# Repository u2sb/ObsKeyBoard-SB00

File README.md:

OBS 专业导播键盘，包括硬件 + 软件，适合个人 DIY，价格便宜 500 以内即可搞定。

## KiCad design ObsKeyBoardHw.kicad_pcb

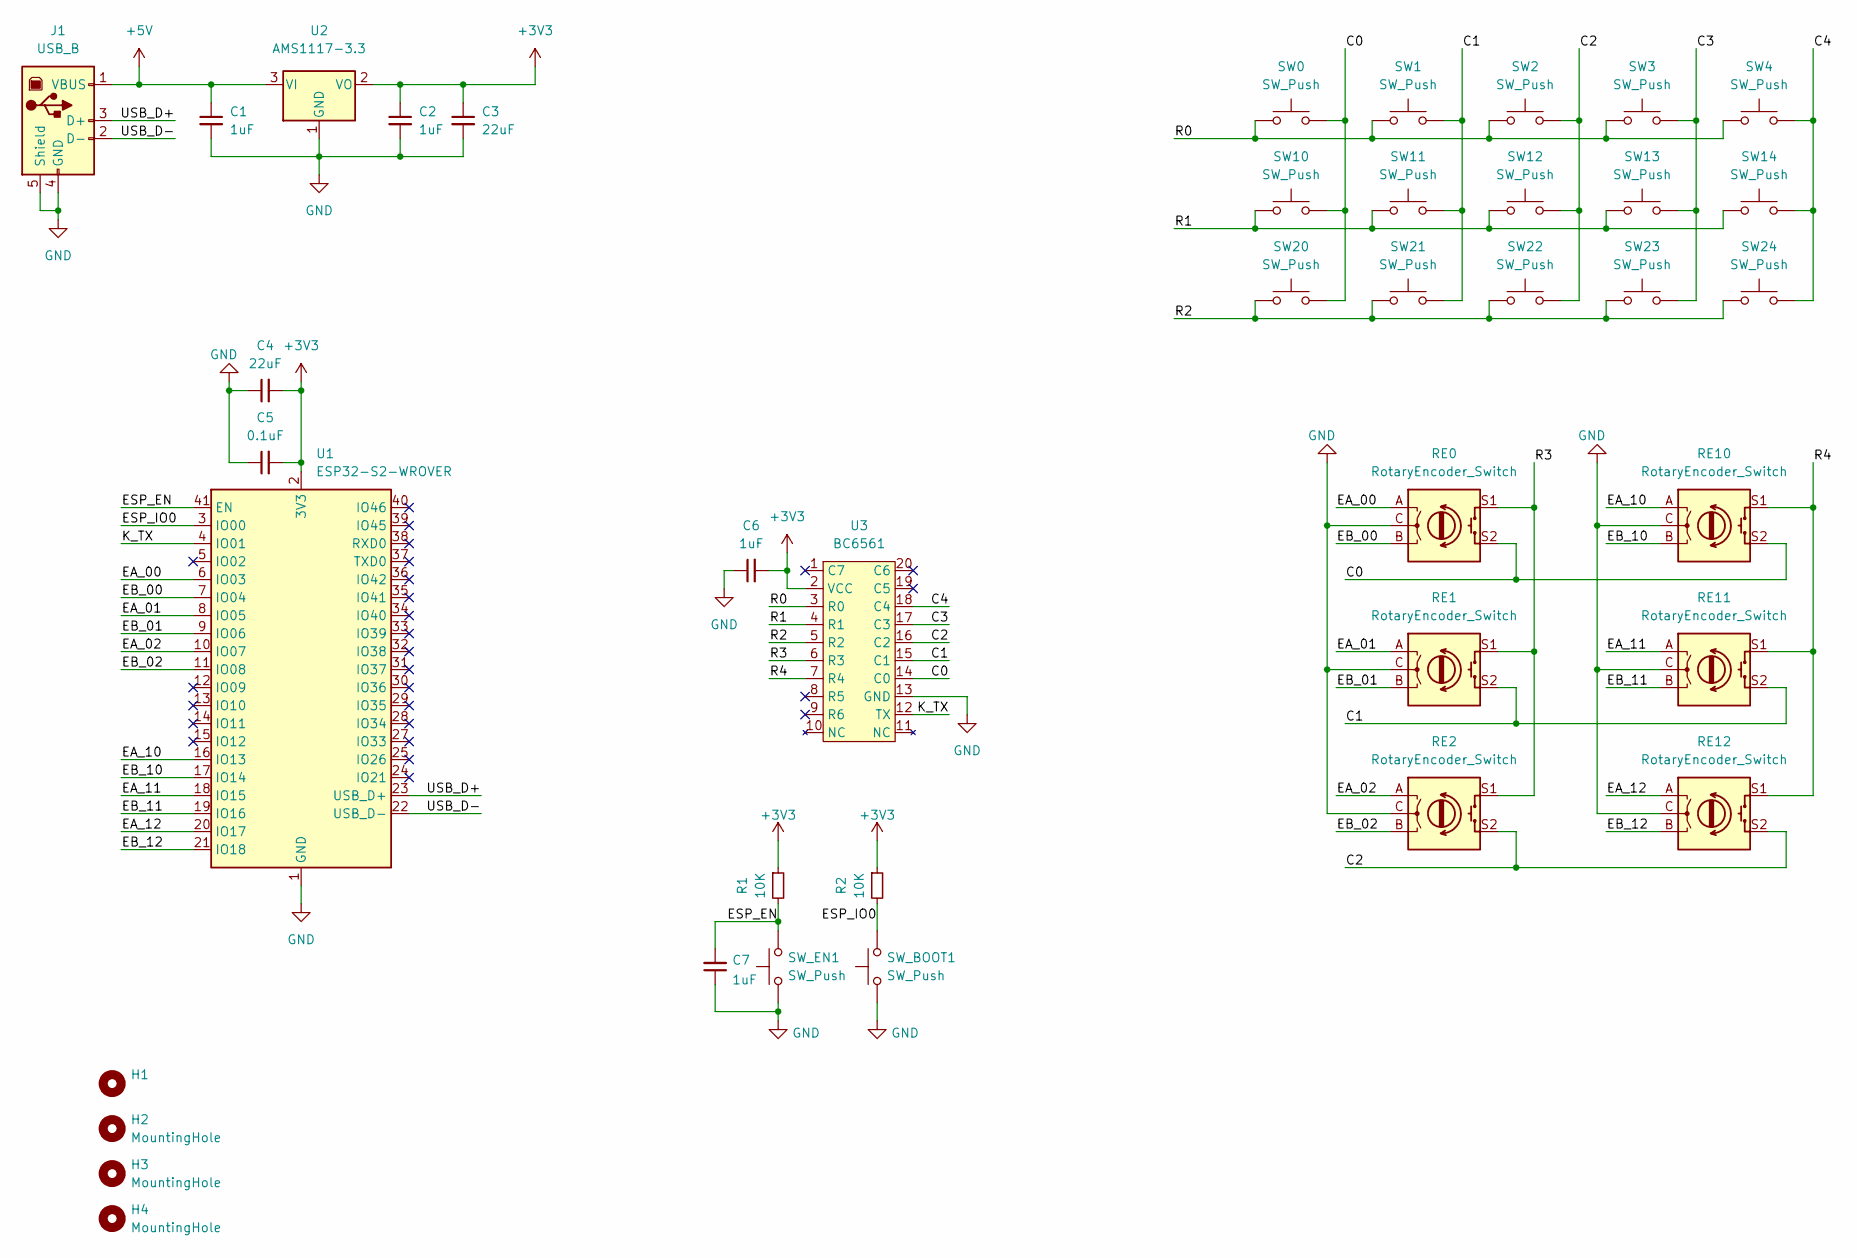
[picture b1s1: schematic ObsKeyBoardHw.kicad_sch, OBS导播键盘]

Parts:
C1, C2, C6, C7: 1uF; C_0805_2012Metric
C3, C4: 22uF; C_0805_2012Metric
C5: 0.1uF; C_0805_2012Metric
H1: (no value)
H2, H3, H4: MountingHole; MountingHole_3.2mm_M3_ISO7380
J1: USB_B; USB_B_Lumberg_2411_02_Horizontal
R1, R2: 10K; R_0805_2012Metric
RE0, RE1, RE2, RE10, RE11, RE12: RotaryEncoder_Switch; RotaryEncoder_Alps_EC11E-Switch_Vertical_H20mm
SW0, SW1, SW2, SW3, SW4, SW10, SW11, SW12, SW13, SW14, SW20, SW21, SW22, SW23, SW24: SW_Push; SW_Cherry_MX_1.00u_Plate
SW_BOOT1: SW_Push; SW_SPST_CK_RS282G05A3
SW_EN1: SW_Push; SW_SPST_CK_RS282G05A3
U1: ESP32-S2-WROVER
U2: AMS1117-3.3; SOT-223-3_TabPin2
U3: BC6561; SSOP-20_5.3x7.2mm_P0.65mm

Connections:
+3V3: C2.1, C3.1, C4.2, C5.2, C6.2, R1.1, R2.1, U1.2 (3V3), U2.2 (VO), U3.2 (VCC)
+5V: C1.1, J1.1 (VBUS), U2.3 (VI)
/C0: RE0.S2, RE10.S2, SW0.2, SW10.2, SW20.2, U3.14 (C0)
/C1: RE1.S2, RE11.S2, SW1.2, SW11.2, SW21.2, U3.15 (C1)
/C2: RE2.S2, RE12.S2, SW2.2, SW12.2, SW22.2, U3.16 (C2)
/C3: SW3.2, SW13.2, SW23.2, U3.17 (C3)
/C4: SW4.2, SW14.2, SW24.2, U3.18 (C4)
/EA_00: RE0.A, U1.6 (IO03)
/EA_01: RE1.A, U1.8 (IO05)
/EA_02: RE2.A, U1.10 (IO07)
/EA_10: RE10.A, U1.16 (IO13)
/EA_11: RE11.A, U1.18 (IO15)
/EA_12: RE12.A, U1.20 (IO17)
/EB_00: RE0.B, U1.7 (IO04)
/EB_01: RE1.B, U1.9 (IO06)
/EB_02: RE2.B, U1.11 (IO08)
/EB_10: RE10.B, U1.17 (IO14)
/EB_11: RE11.B, U1.19 (IO16)
/EB_12: RE12.B, U1.21 (IO18)
/ESP_EN: C7.2, R1.2, SW_EN1.2, U1.41 (EN)
/ESP_IO0: R2.2, SW_BOOT1.2, U1.3 (IO00)
/K_TX: U1.4 (IO01), U3.12 (TX)
/R0: SW0.1, SW1.1, SW2.1, SW3.1, SW4.1, U3.3 (R0)
/R1: SW10.1, SW11.1, SW12.1, SW13.1, SW14.1, U3.4 (R1)
/R2: SW20.1, SW21.1, SW22.1, SW23.1, SW24.1, U3.5 (R2)
/R3: RE0.S1, RE1.S1, RE2.S1, U3.6 (R3)
/R4: RE10.S1, RE11.S1, RE12.S1, U3.7 (R4)
/USB_D+: J1.3 (D+), U1.23 (USB_D+)
/USB_D-: J1.2 (D-), U1.22 (USB_D-)
GND: C1.2, C2.2, C3.2, C4.1, C5.1, C6.1, C7.1, J1.4 (GND), J1.5 (Shield), RE0.C, RE1.C, RE2.C, RE10.C, RE11.C, RE12.C, SW_BOOT1.1, SW_EN1.1, U1.1 (GND), U1.26 (GND), U1.42 (GND), U1.43 (GND), U2.1 (GND), U3.13 (GND)

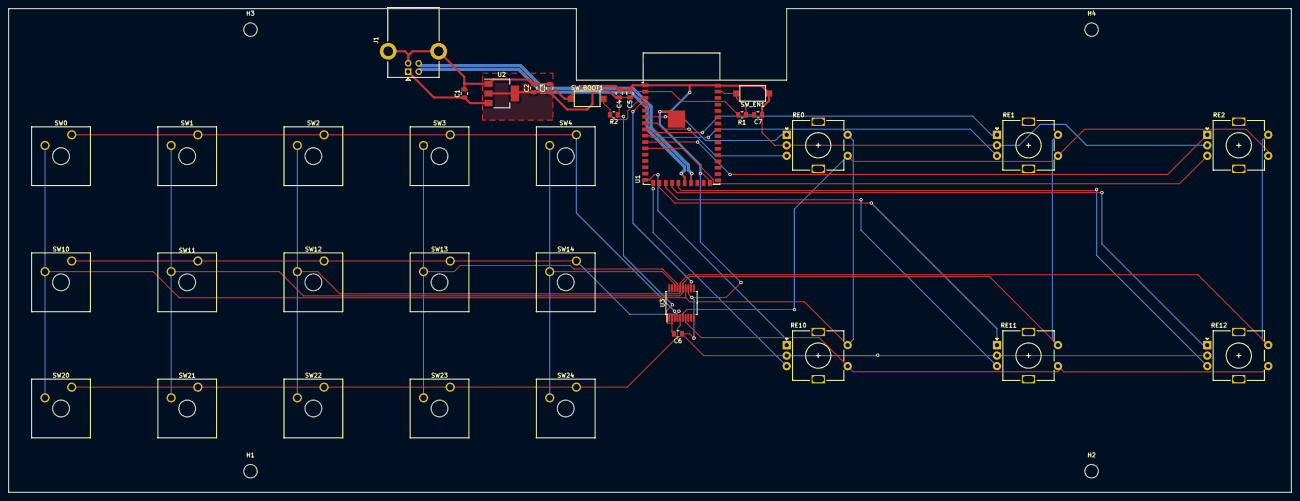
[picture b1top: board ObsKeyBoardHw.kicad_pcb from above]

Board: 2 copper layers, 305.0 x 115.0 mm, 40 parts (0 on the bottom side), 30 nets.

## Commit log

2022-05-06 初始版本
2022-05-09 添加外壳
2022-05-09 更新标题
2022-05-10 更新固件
2022-05-11 更新程序
2022-05-12 更新目录结构
2022-05-12 更新固件介绍
2022-10-17 支持OBS28
2022-10-29 更新固件和上位机
2022-10-29 更新上位机
2022-10-31 更新上位机算法
2022-10-31 增加数据校验机制
